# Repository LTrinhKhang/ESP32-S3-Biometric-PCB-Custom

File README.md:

# ESP32-S3 Biometric Attendance – Custom PCB Design

## Project Overview

This project presents a custom 2-layer PCB designed for a biometric attendance device based on ESP32-S3.  
The design integrates power management, high-speed SPI routing, and mixed-signal layout considerations in a compact form factor.

---
# Schematic Overview

---

## PCB Layout Overview

### Top Copper Layer

### Bottom Copper Layer

---

## Power Stage Layout (Buck Converter Optimization)

### Buck Layout – Hot Loop Minimization

The TPS62130 switching regulator layout prioritizes:

- Minimal VIN → SW → Inductor → CIN return loop area  
- Short SW node (~3 mm) to reduce radiated EMI  
- Tight PGND current return  
- Input capacitor placed within millimeters of VIN and PGND pins  

---

## 3D Board Rendering

### 3D Top View

### 3D Bottom View

---

## Hardware Specifications

- **Layer Count**: 2-layer FR4  
- **Copper Weight**: 1 oz  
- **Board Size**: 70 × 44 mm  
- **Min Trace/Space**: 0.15 mm  
- **Min Drill**: 0.30 mm  
- **Ground Strategy**: Continuous bottom ground plane  

---

## Power Design

- **Regulator**: Step-down buck converter (3.0–4.2V → 3.3V)  
- **Controller**: TPS62130 (~2.4 MHz switching frequency)  
- **Optimization**:
  - Minimized hot loop area  
  - Proper CIN placement  
  - Thermal vias under IC  
  - Wide 3.3V power rail  

---

## Current & Trace Width Justification

The 3.3V rail supports up to **1.5A load current**, including:

- ESP32-S3 WiFi burst current  
- TFT backlight  
- Fingerprint sensor  
- Safety design margin  

Based on IPC-2152 trace width calculation (1 oz copper, 20°C rise):

- Required trace width ≈ 0.8 mm  
- Implemented trace width = 1.5 mm  

This reduces voltage drop and improves transient stability during high current spikes.

---

## EMI Consideration

Due to high dv/dt and di/dt at the switching node:

- SW trace length minimized (~3 mm)  
- Loop inductance reduced to limit ringing  
- Ground return path kept compact  
- No signal routing under SW node  
- ESP32 antenna keepout strictly respected  

Increasing SW trace length (e.g., 15 mm) would increase loop inductance and radiated EMI.

---

## RF Considerations

- Antenna keepout region respected  
- No copper or ground plane under antenna  
- Controlled ground reference near RF section  

These measures preserve WiFi/BT performance.

---

## Manufacturing

**During DRC validation, the following were corrected:**

- Hole clearance violations resolved  
- Drill size adjusted from 0.2 mm → 0.3 mm  
- Thermal relief optimized  
- Via stitching added for current spreading  
- Final DRC: clean before Gerber generation  

Fully compatible with standard fabrication services (JLCPCB, PCBWay).

---

## Future Improvements

- 4-layer stackup for improved EMI control and return path integrity  
- Further decoupling network optimization  
- Dedicated RF ground stitching zone

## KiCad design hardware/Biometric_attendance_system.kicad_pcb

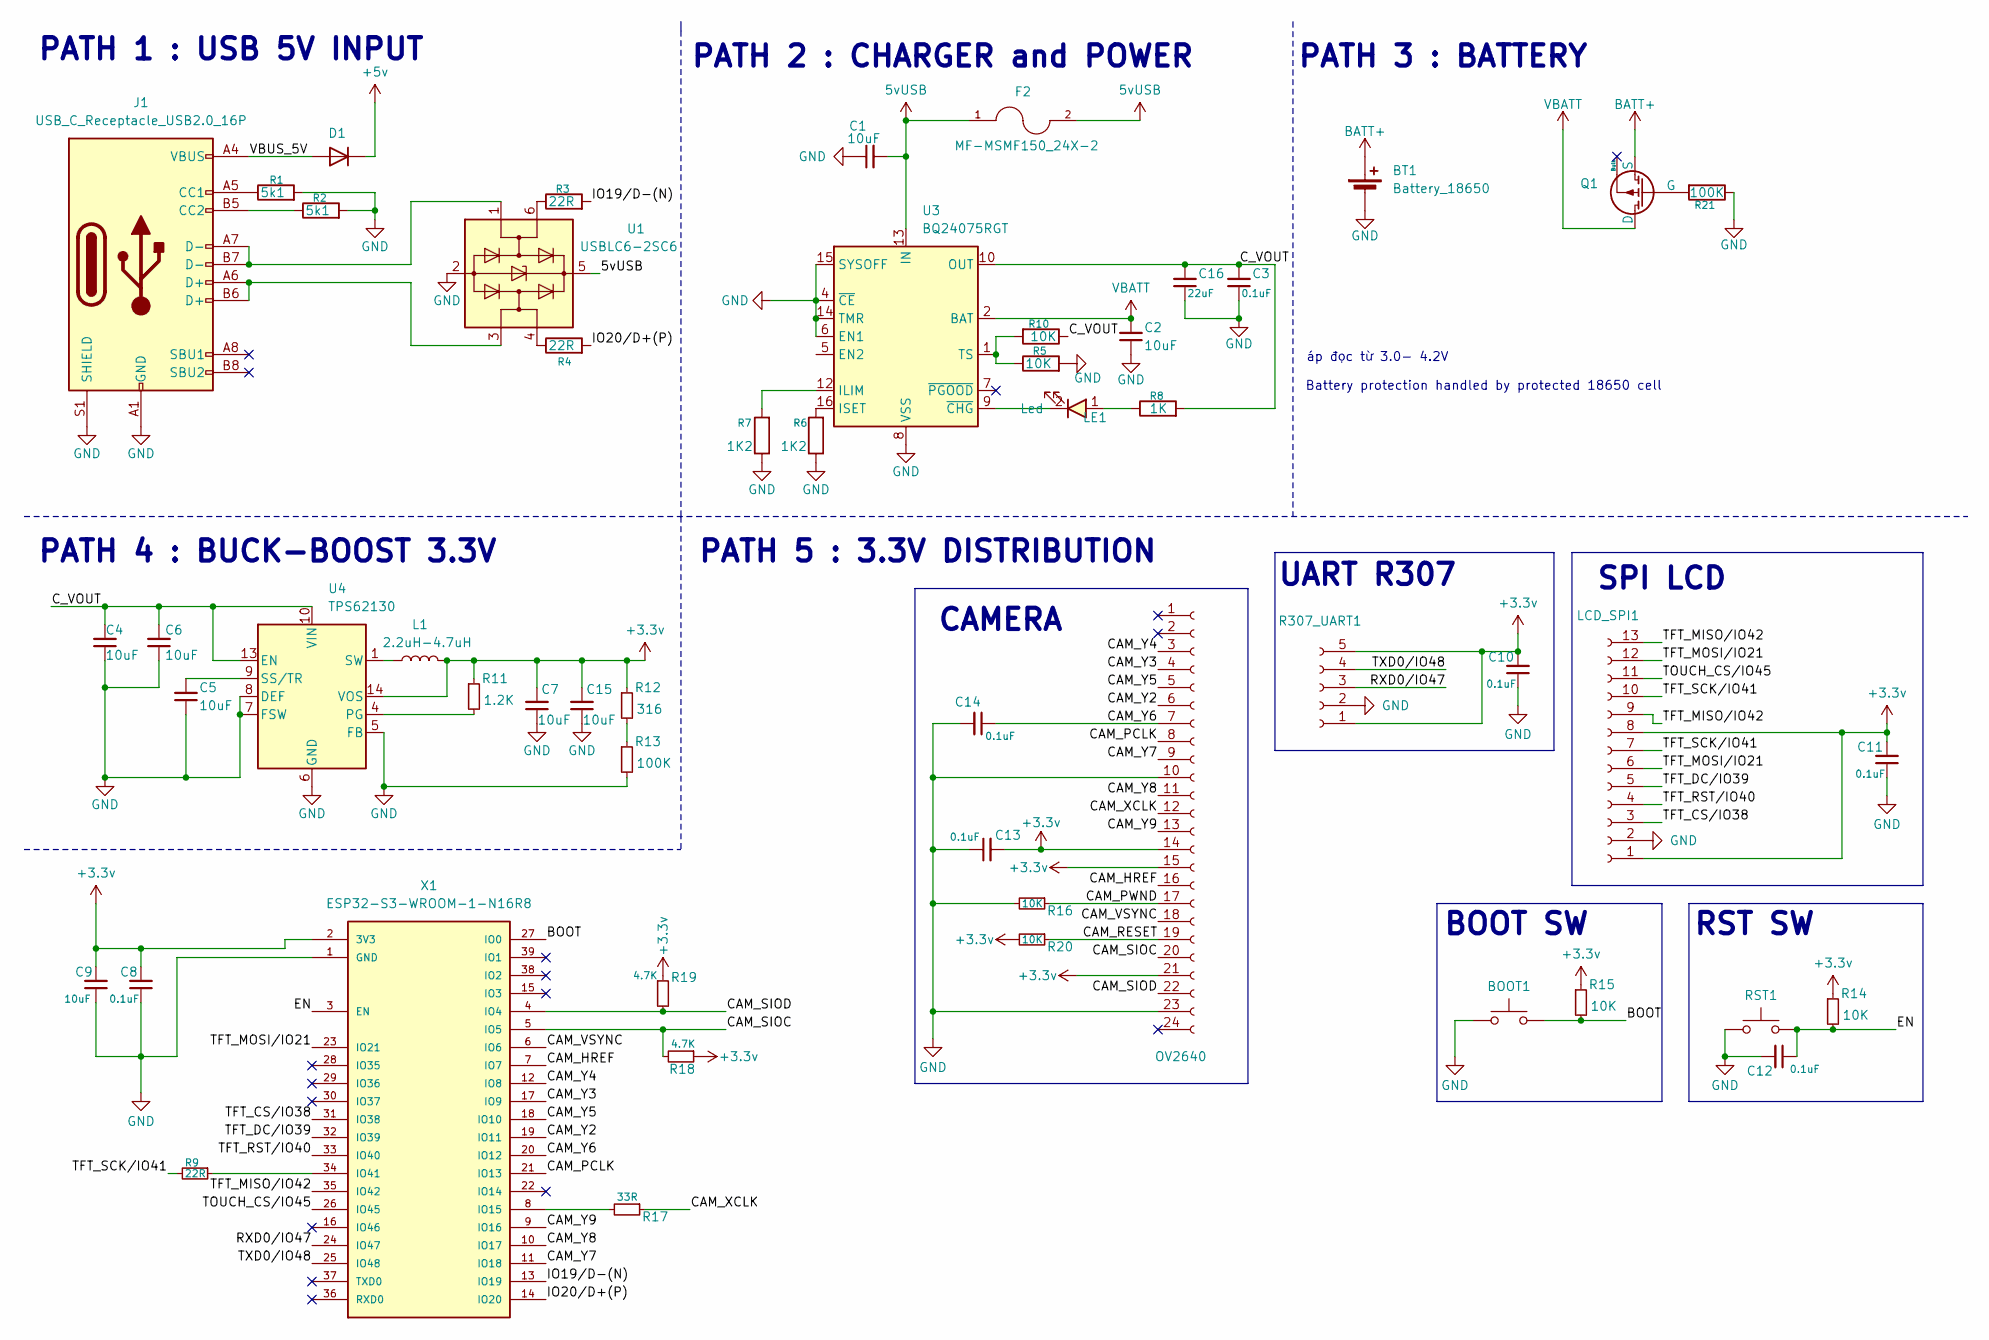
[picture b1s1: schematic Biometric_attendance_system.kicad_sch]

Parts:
BOOT1: SW_Push; SW_Push_SPST_NO_Alps_SKRK
BT1: Battery_18650; JST_PH_B2B-PH-K_1x02_P2.00mm_Vertical
C1, C2, C4, C5, C6, C7, C9, C15: 10uF; C_0603
C3, C8, C10, C11, C12, C13, C14: 0.1uF; C_0603
C16: 22uF; C_0603
D1: D; Package-Diode-D_SMA
F2: MF-MSMF150_24X-2; FUSER_MF-MSMF150_24X-2
J1: USB_C_Receptacle_USB2.0_16P; USB_C_Receptacle_GCT_USB4105-xx-A_16P_TopMnt_Horizontal
L1: 2.2uH-4.7uH; L_0603
LCD_SPI1: Conn_01x13_Socket; PinHeader_1x13_P2.54mm_Vertical
LE1: Led; LED_0603
OV2640: Conn_01x24_Socket; TE_2-1734839-4_1x24-1MP_P0.5mm_Horizontal
Q1: PMOS_Substrate; SOT-23
R1, R2: 5k1; R_0603
R3, R4, R9: 22R; R_0603
R5, R10, R14, R15, R16, R20: 10K; R_0603
R6, R7: 1K2; R_0603
R8: 1K; R_0603
R11: 1.2K; R_0603
R12: 316; R_0603
R13, R21: 100K; R_0603
R17: 33R; R_0603
R18, R19: 4.7K; R_0603
R307_UART1: Conn_01x05_Socket; PinHeader_1x05_P1.00mm_Vertical
RST1: SW_Push; SW_Push_SPST_NO_Alps_SKRK
U1: USBLC6-2SC6; SOT-23-6
U3: BQ24075RGT; VQFN-16-1EP_3x3mm_P0.5mm_EP1.6x1.6mm
U4: TPS62130; VQFN-16-1EP_3x3mm_P0.5mm_EP1.68x1.68mm_ThermalVias
X1: ESP32-S3-WROOM-1-N16R8; ESP32S3WROOM1N8R2; MANUFACTURER_PART_NUMBER ESP32-S3-WROOM-1-N16R8

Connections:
5vUSB: C1.2, F2.1, F2.2, U1.5 (VBUS), U3.13 (IN)
+3.3v: C7.2, C8.2, C9.2, C10.2, C11.2, C13.2, C15.2, L1.2, LCD_SPI1.1, LCD_SPI1.8, OV2640.14, OV2640.15, OV2640.21, R11.1, R12.1, R14.1, R15.1, R18.1, R19.1, R20.2, R307_UART1.1, R307_UART1.5, U4.14 (VOS), X1.2 (3V3)
+5v: D1.1 (K)
/BOOT: BOOT1.2, R15.2, X1.27 (IO0)
/CAM_HREF: OV2640.16, X1.7 (IO7)
/CAM_PCLK: OV2640.8, X1.21 (IO13)
/CAM_PWND: OV2640.17, R16.1
/CAM_RESET: OV2640.19, R20.1
/CAM_SIOC: OV2640.20, R18.2, X1.5 (IO5)
/CAM_SIOD: OV2640.22, R19.2, X1.4 (IO4)
/CAM_VSYNC: OV2640.18, X1.6 (IO6)
/CAM_XCLK: OV2640.12, R17.1
/CAM_Y2: OV2640.6, X1.19 (IO11)
/CAM_Y3: OV2640.4, X1.17 (IO9)
/CAM_Y4: OV2640.3, X1.12 (IO8)
/CAM_Y5: OV2640.5, X1.18 (IO10)
/CAM_Y6: C14.1, OV2640.7, X1.20 (IO12)
/CAM_Y7: OV2640.9, X1.11 (IO18)
/CAM_Y8: OV2640.11, X1.10 (IO17)
/CAM_Y9: OV2640.13, X1.9 (IO16)
/C_VOUT: C3.2, C4.2, C6.2, C16.2, R8.2, R10.1, U3.10 (OUT), U3.11 (OUT), U4.10 (VIN), U4.11 (VIN), U4.12 (VIN), U4.13 (EN)
/EN: C12.1, R14.2, RST1.2, X1.3 (EN)
/IO19/D-(N): R3.2, X1.13 (IO19)
/IO20/D+(P): R4.2, X1.14 (IO20)
/RXD0/IO47: R307_UART1.3, X1.24 (IO47)
/TFT_CS/IO38: LCD_SPI1.3, X1.31 (IO38)
/TFT_DC/IO39: LCD_SPI1.5, X1.32 (IO39)
/TFT_MISO/IO42: LCD_SPI1.9, LCD_SPI1.13, X1.35 (IO42)
/TFT_MOSI/IO21: LCD_SPI1.6, LCD_SPI1.12, X1.23 (IO21)
/TFT_RST/IO40: LCD_SPI1.4, X1.33 (IO40)
/TFT_SCK/IO41: LCD_SPI1.7, LCD_SPI1.10, R9.2
/TOUCH_CS/IO45: LCD_SPI1.11, X1.26 (IO45)
/TXD0/IO48: R307_UART1.4, X1.25 (IO48)
/VBUS_5V: D1.2 (A), J1.A4 (VBUS), J1.A9 (VBUS), J1.B4 (VBUS), J1.B9 (VBUS)
BATT+: BT1.1 (+), Q1.3 (S)
GND: BOOT1.1, BT1.2 (-), C1.1, C2.1, C3.1, C4.1, C5.1, C6.1, C7.1, C8.1, C9.1, C10.1, C11.1, C12.2, C13.1, C14.2, C15.1, C16.1, J1.A1 (GND), J1.A12 (GND), J1.B1 (GND), J1.B12 (GND), J1.S1 (SHIELD), LCD_SPI1.2, OV2640.10, OV2640.23, R1.2, R2.2, R5.2, R6.1, R7.1, R13.2, R16.2, R21.1, R307_UART1.2, RST1.1, U1.2 (GND), U3.4 (~CE), U3.5 (EN2), U3.6 (EN1), U3.8 (VSS), U3.14 (TMR), U3.15 (SYSOFF), U3.17 (VSS), U4.5 (FB), U4.6 (GND), U4.7 (FSW), U4.8 (DEF), U4.15 (GND), U4.16 (GND), U4.17 (GND), X1.1 (GND), X1.40 (GND), X1.41 (GND), X1.42 (GND), X1.43 (GND), X1.44 (GND), X1.45 (GND), X1.46 (GND), X1.47 (GND), X1.48 (GND), X1.49 (GND)
unnamed: J1.A5 (CC1), R1.1
unnamed: J1.B5 (CC2), R2.1
unnamed: J1.A6 (D+), J1.B6 (D+), U1.3 (I/O2)
unnamed: J1.A7 (D-), J1.B7 (D-), U1.1 (I/O1)
unnamed: L1.1, U4.1 (SW), U4.2 (SW), U4.3 (SW)
unnamed: LE1.1, R8.1
unnamed: Q1.2 (G), R21.2
unnamed: R3.1, U1.6 (I/O1)
unnamed: R4.1, U1.4 (I/O2)
unnamed: R12.2, R13.1
unnamed: R7.2, U3.12 (ILIM)
unnamed: R6.2, U3.16 (ISET)
unnamed: R5.1, R10.2, U3.1 (TS)
unnamed: LE1.2, U3.9 (~CHG)
unnamed: R11.2, U4.4 (PG)
unnamed: C5.2, U4.9 (SS/TR)
unnamed: R17.2, X1.8 (IO15)
unnamed: R9.1, X1.34 (IO41)
VBATT: C2.2, Q1.1 (D), U3.2 (BAT), U3.3 (BAT)

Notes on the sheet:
UART R307
SPI LCD
PATH 5 : 3.3V DISTRIBUTION
PATH 4 : BUCK-BOOST 3.3V
PATH 2 : CHARGER and POWER
CAMERA
áp đọc từ 3.0- 4.2V
PATH 3 : BATTERY
BOOT SW
Battery protection handled by protected 18650 cell
PATH 1 : USB 5V INPUT
RST SW

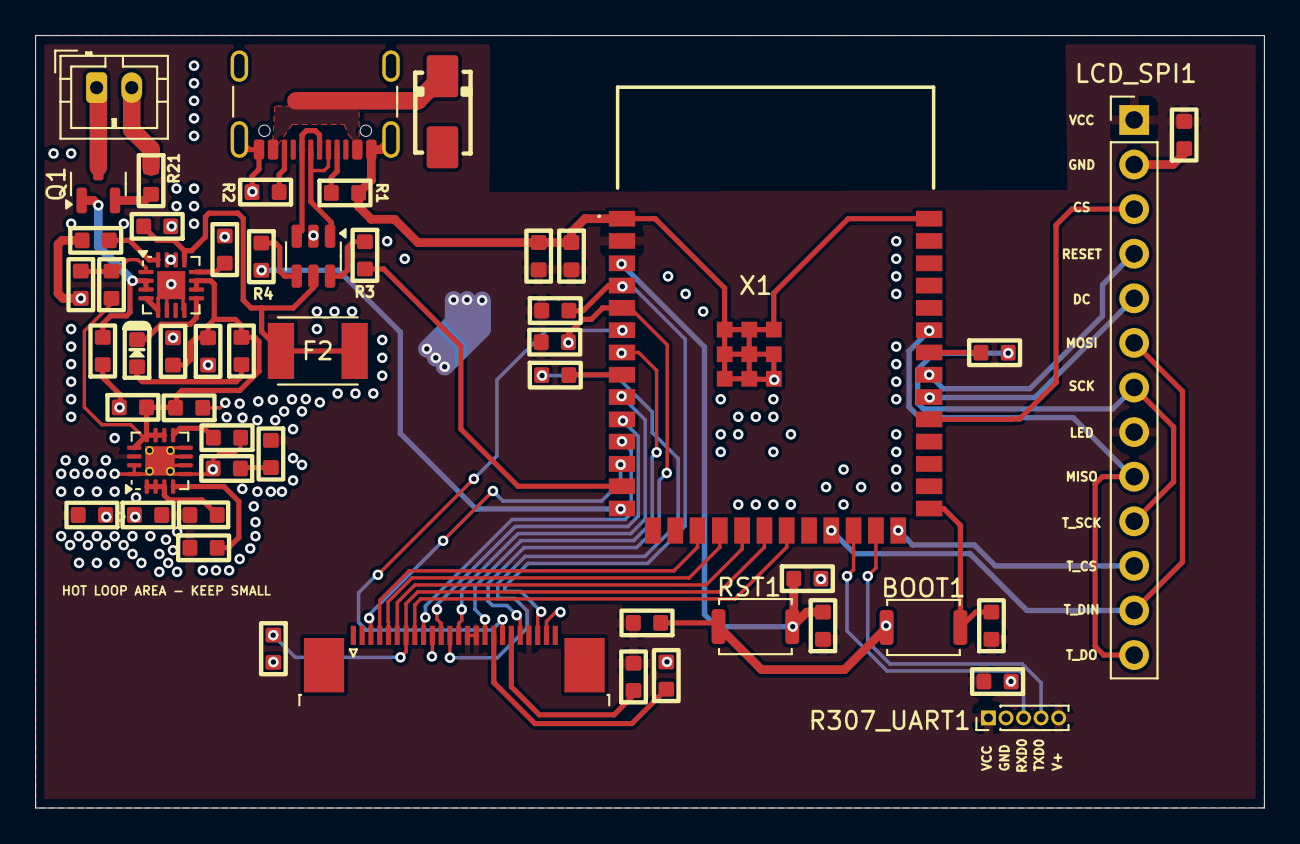
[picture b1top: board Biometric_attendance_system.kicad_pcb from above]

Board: 2 copper layers, 70.0 x 44.0 mm, 53 parts (0 on the bottom side), 54 nets.

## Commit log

2026-02-24 Initial commit - Full ESP32 S3 Biometric PCB
2026-02-26 Fix formatting of section headers in README.md
